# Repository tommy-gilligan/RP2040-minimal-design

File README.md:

# RP2040 Minimal Design for JLCPCB
Based on [Minimal design example](https://datasheets.raspberrypi.com/rp2040/Minimal-KiCAD.zip) referenced in [Hardware design with RP2040: Using RP2040 microcontrollers to build boards and products](https://datasheets.raspberrypi.com/rp2040/hardware-design-with-rp2040.pdf).  Design updated for KiCAD 7 and manufacture/assembly at JLCPCB.

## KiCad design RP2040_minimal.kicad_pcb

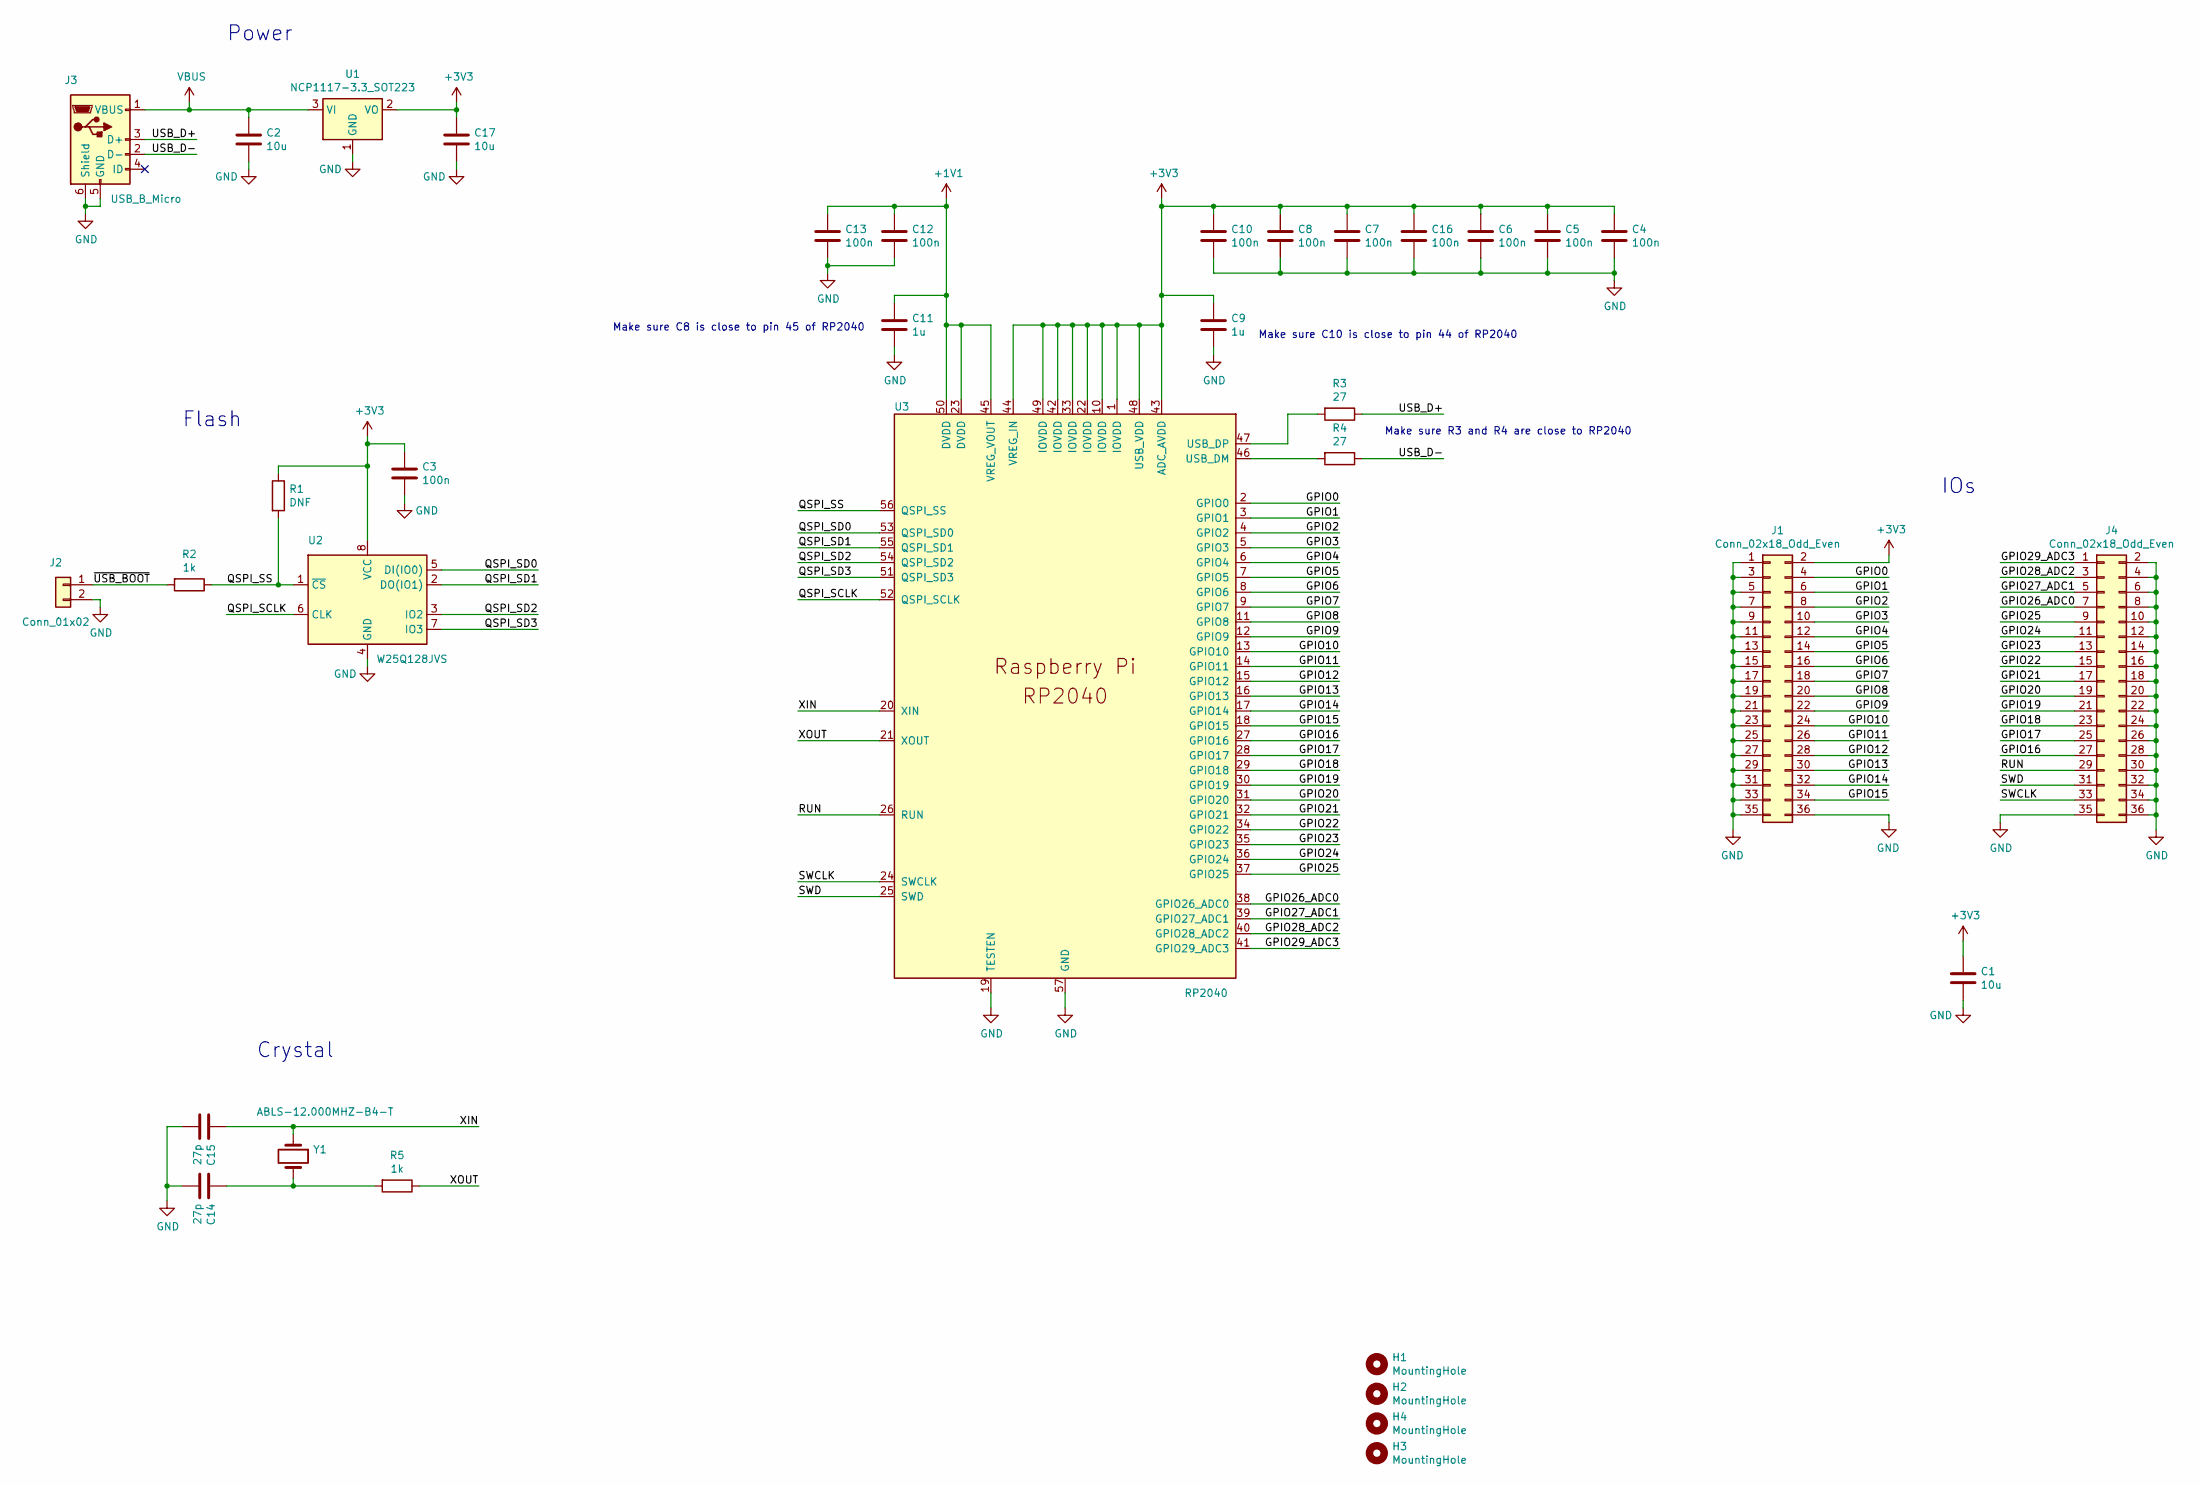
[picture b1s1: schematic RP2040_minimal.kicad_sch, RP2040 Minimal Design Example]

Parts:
C1, C2, C17: 10u; C_0805_2012Metric; LCSC C15850
C3, C4, C5, C6, C7, C8, C10, C12, C13, C16: 100n; C_0402_1005Metric; LCSC C126504
C9, C11: 1u; C_0402_1005Metric; LCSC C307331
C14, C15: 27p; C_0402_1005Metric; LCSC C52923
H1, H2, H3, H4: MountingHole; MountingHole_2.7mm_M2.5
J1, J4: Conn_02x18_Odd_Even; PinHeader_2x18_P2.54mm_Vertical; LCSC C168945
J2: Conn_01x02; PinHeader_1x02_P2.54mm_Vertical; LCSC C124375
J3: USB_B_Micro; USB_Micro-B_Amphenol_10103594-0001LF_Horizontal_modified; LCSC C428495
R1: DNF; C_0402_1005Metric
R2, R5: 1k; C_0402_1005Metric; LCSC C11702
R3, R4: 27; C_0402_1005Metric; LCSC C274349
U1: NCP1117-3.3_SOT223; SOT-223-3_TabPin2; LCSC C26537
U2: W25Q128JVS; SOIC-8_5.23x5.23mm_P1.27mm; LCSC C97521
U3: RP2040; RP2040-QFN-56; LCSC C2040
Y1: ABLS-12.000MHZ-B4-T; Crystal_SMD_HC49-US; LCSC C110563

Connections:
+1V1: C11.1, C12.1, C13.1, U3.23 (DVDD), U3.45 (VREG_VOUT), U3.50 (DVDD)
+3V3: C1.1, C3.1, C4.1, C5.1, C6.1, C7.1, C8.1, C9.1, C10.1, C16.1, C17.1, J1.2, R1.1, U1.2 (VO), U2.8 (VCC), U3.1 (IOVDD), U3.10 (IOVDD), U3.22 (IOVDD), U3.33 (IOVDD), U3.42 (IOVDD), U3.43 (ADC_AVDD), U3.44 (VREG_IN), U3.48 (USB_VDD), U3.49 (IOVDD)
/GPIO0: J1.4, U3.2 (GPIO0)
/GPIO1: J1.6, U3.3 (GPIO1)
/GPIO2: J1.8, U3.4 (GPIO2)
/GPIO3: J1.10, U3.5 (GPIO3)
/GPIO4: J1.12, U3.6 (GPIO4)
/GPIO5: J1.14, U3.7 (GPIO5)
/GPIO6: J1.16, U3.8 (GPIO6)
/GPIO7: J1.18, U3.9 (GPIO7)
/GPIO8: J1.20, U3.11 (GPIO8)
/GPIO9: J1.22, U3.12 (GPIO9)
/GPIO10: J1.24, U3.13 (GPIO10)
/GPIO11: J1.26, U3.14 (GPIO11)
/GPIO12: J1.28, U3.15 (GPIO12)
/GPIO13: J1.30, U3.16 (GPIO13)
/GPIO14: J1.32, U3.17 (GPIO14)
/GPIO15: J1.34, U3.18 (GPIO15)
/GPIO16: J4.27, U3.27 (GPIO16)
/GPIO17: J4.25, U3.28 (GPIO17)
/GPIO18: J4.23, U3.29 (GPIO18)
/GPIO19: J4.21, U3.30 (GPIO19)
/GPIO20: J4.19, U3.31 (GPIO20)
/GPIO21: J4.17, U3.32 (GPIO21)
/GPIO22: J4.15, U3.34 (GPIO22)
/GPIO23: J4.13, U3.35 (GPIO23)
/GPIO24: J4.11, U3.36 (GPIO24)
/GPIO25: J4.9, U3.37 (GPIO25)
/GPIO26_ADC0: J4.7, U3.38 (GPIO26_ADC0)
/GPIO27_ADC1: J4.5, U3.39 (GPIO27_ADC1)
/GPIO28_ADC2: J4.3, U3.40 (GPIO28_ADC2)
/GPIO29_ADC3: J4.1, U3.41 (GPIO29_ADC3)
/QSPI_SCLK: U2.6 (CLK), U3.52 (QSPI_SCLK)
/QSPI_SD0: U2.5 (DI(IO0)), U3.53 (QSPI_SD0)
/QSPI_SD1: U2.2 (DO(IO1)), U3.55 (QSPI_SD1)
/QSPI_SD2: U2.3 (IO2), U3.54 (QSPI_SD2)
/QSPI_SD3: U2.7 (IO3), U3.51 (QSPI_SD3)
/QSPI_SS: R1.2, R2.1, U2.1 (~CS), U3.56 (QSPI_SS)
/RUN: J4.29, U3.26 (RUN)
/SWCLK: J4.33, U3.24 (SWCLK)
/SWD: J4.31, U3.25 (SWD)
/USB_D+: J3.3 (D+), R3.1
/USB_D-: J3.2 (D-), R4.1
/XIN: C15.1, U3.20 (XIN), Y1.1
/XOUT: R5.1, U3.21 (XOUT)
/~USB_BOOT: J2.1, R2.2
GND: C1.2, C2.2, C3.2, C4.2, C5.2, C6.2, C7.2, C8.2, C9.2, C10.2, C11.2, C12.2, C13.2, C14.2, C15.2, C16.2, C17.2, J1.1, J1.3, J1.5, J1.7, J1.9, J1.11, J1.13, J1.15, J1.17, J1.19, J1.21, J1.23, J1.25, J1.27, J1.29, J1.31, J1.33, J1.35, J1.36, J2.2, J3.5 (GND), J3.6 (Shield), J4.2, J4.4, J4.6, J4.8, J4.10, J4.12, J4.14, J4.16, J4.18, J4.20, J4.22, J4.24, J4.26, J4.28, J4.30, J4.32, J4.34, J4.35, J4.36, U1.1 (GND), U2.4 (GND), U3.19 (TESTEN), U3.57 (GND)
unnamed: C14.1, R5.2, Y1.2
unnamed: R4.2, U3.46 (USB_DM)
unnamed: R3.2, U3.47 (USB_DP)
VBUS: C2.1, J3.1 (VBUS), U1.3 (VI)

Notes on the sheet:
IOs
Make sure C8 is close to pin 45 of RP2040
Make sure C10 is close to pin 44 of RP2040
Crystal
Power
Flash
Make sure R3 and R4 are close to RP2040

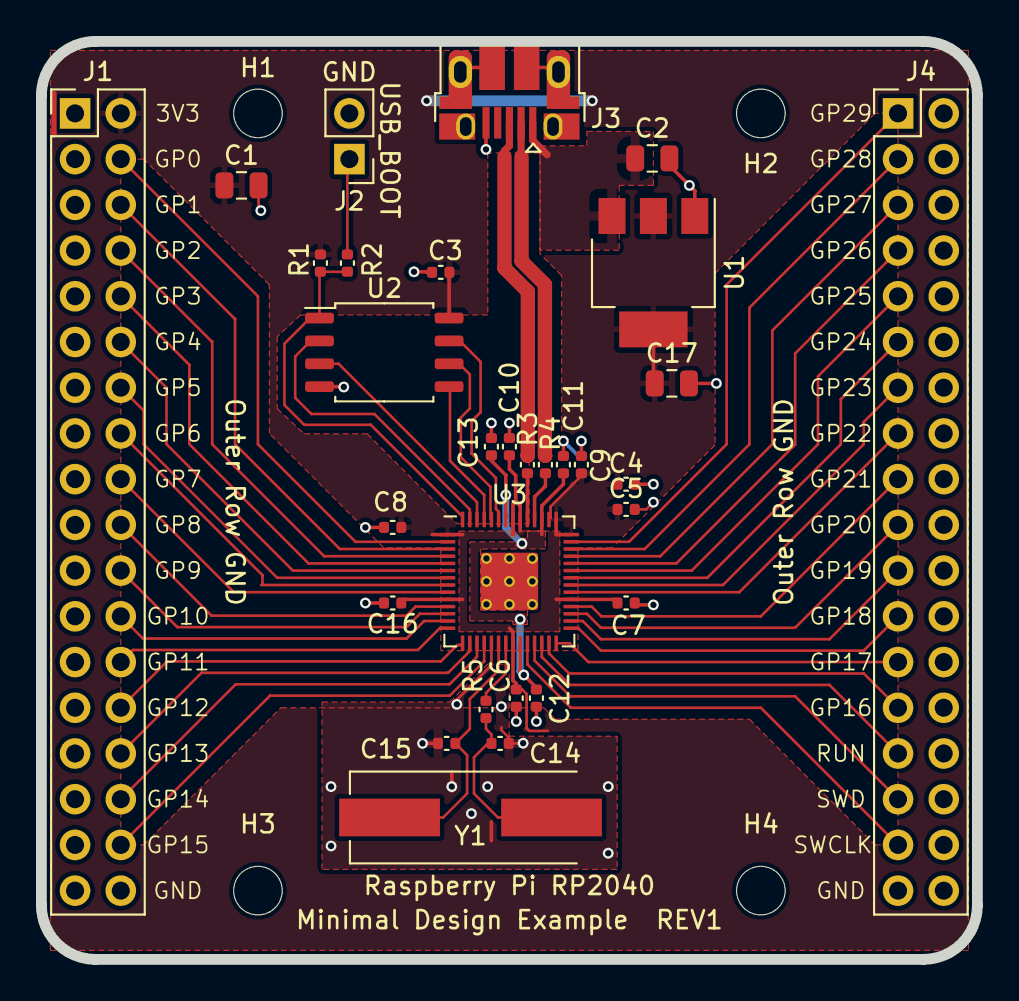
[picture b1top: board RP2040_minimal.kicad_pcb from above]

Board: 2 copper layers, 52.0 x 51.0 mm, 34 parts (0 on the bottom side), 51 nets.

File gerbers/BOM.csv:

Comment,Designator,Footprint,"LCSC Part Number"
"10u","C1,C2,C17","Capacitor_SMD:C_0805_2012Metric","C15850"
"27p","C14,C15","Capacitor_SMD:C_0402_1005Metric","C52923"
"100n","C3,C4,C5,C6,C7,C8,C10,C12,C13,C16","Capacitor_SMD:C_0402_1005Metric","C126504"
"1u","C9,C11","Capacitor_SMD:C_0402_1005Metric","C307331"
"MountingHole","H1,H2,H3,H4","MountingHole:MountingHole_2.7mm_M2.5",""
"Conn_02x18_Odd_Even","J1,J4","Connector_PinHeader_2.54mm:PinHeader_2x18_P2.54mm_Vertical","C168945"
"Conn_01x02","J2","Connector_PinHeader_2.54mm:PinHeader_1x02_P2.54mm_Vertical","C124375"
"USB_B_Micro","J3","RP2040_minimal:USB_Micro-B_Amphenol_10103594-0001LF_Horizontal_modified","C428495"
"DNF","R1","Capacitor_SMD:C_0402_1005Metric",""
"1k","R2,R5","Capacitor_SMD:C_0402_1005Metric","C11702"
"27","R3,R4","Capacitor_SMD:C_0402_1005Metric","C274349"
"NCP1117-3.3_SOT223","U1","Package_TO_SOT_SMD:SOT-223-3_TabPin2","C26537"
"W25Q128JVS","U2","Package_SO:SOIC-8_5.23x5.23mm_P1.27mm","C97521"
"RP2040","U3","RP2040_minimal:RP2040-QFN-56","C2040"
"ABLS-12.000MHZ-B4-T","Y1","RP2040_minimal:Crystal_SMD_HC49-US","C110563"

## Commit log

2023-04-13 initial checkin
2023-04-13 get DRC passing
2023-04-13 prepare fabrication outputs
2023-04-13 add license and readme
